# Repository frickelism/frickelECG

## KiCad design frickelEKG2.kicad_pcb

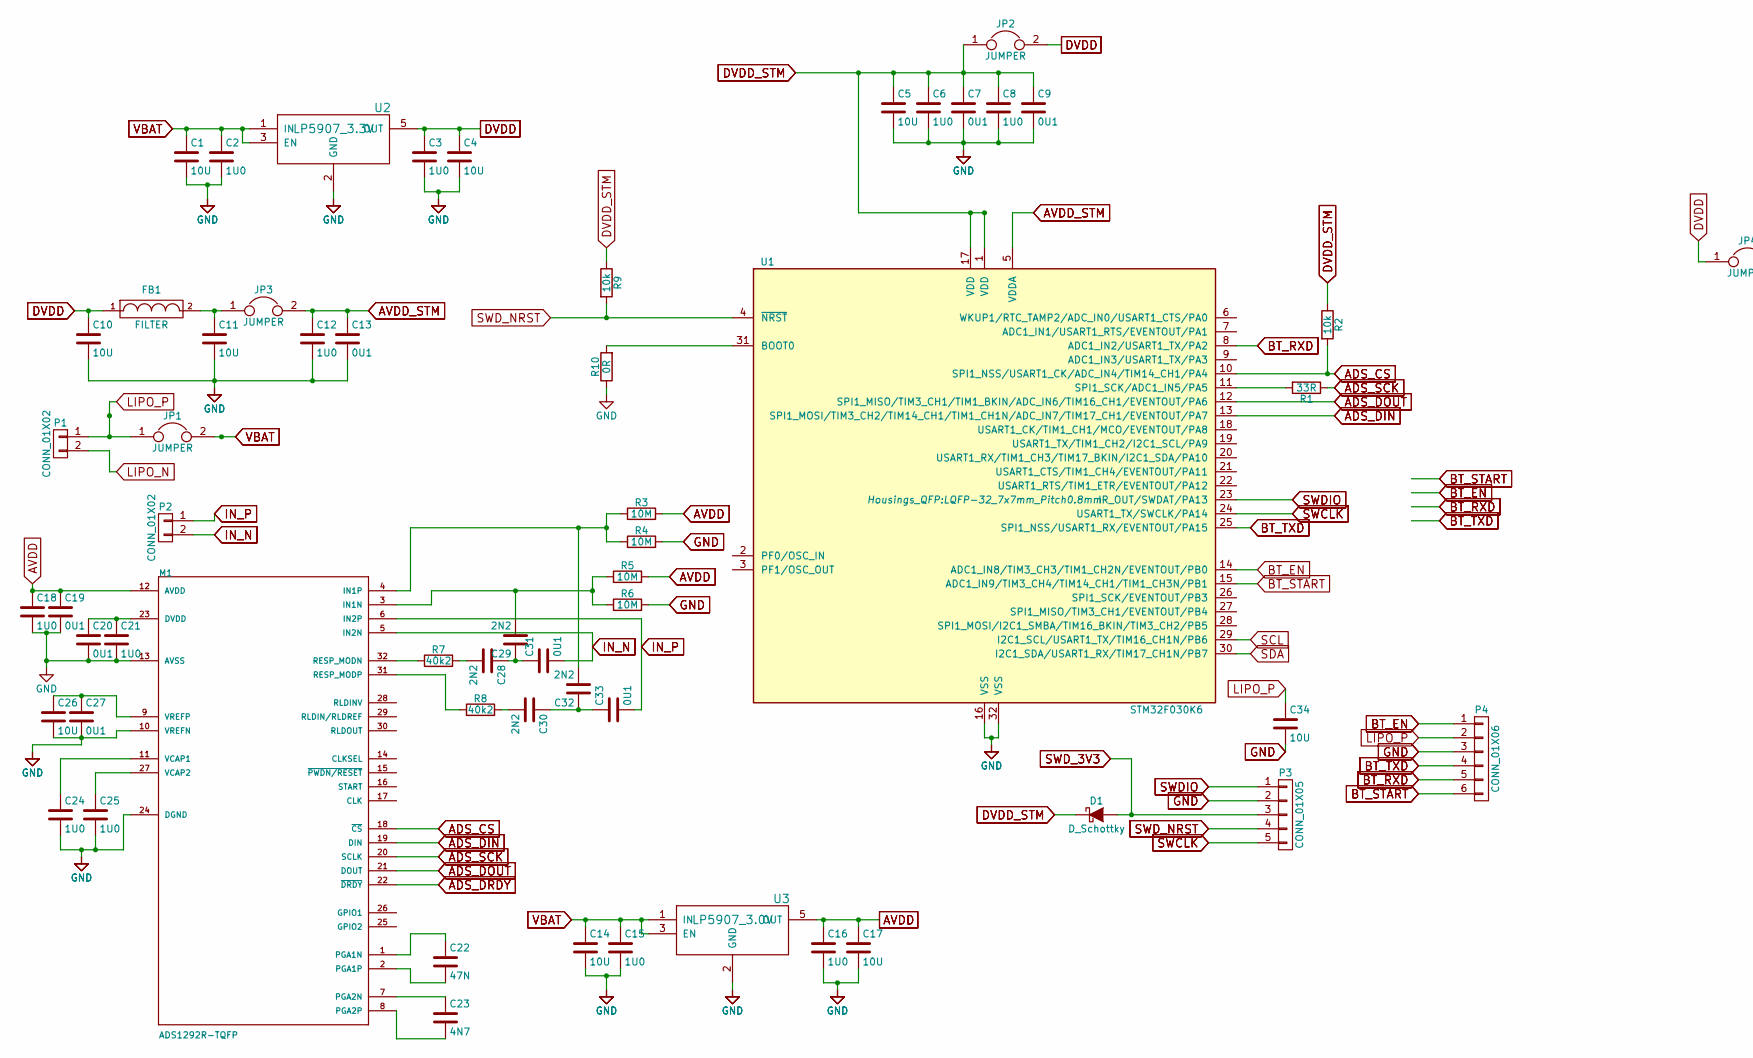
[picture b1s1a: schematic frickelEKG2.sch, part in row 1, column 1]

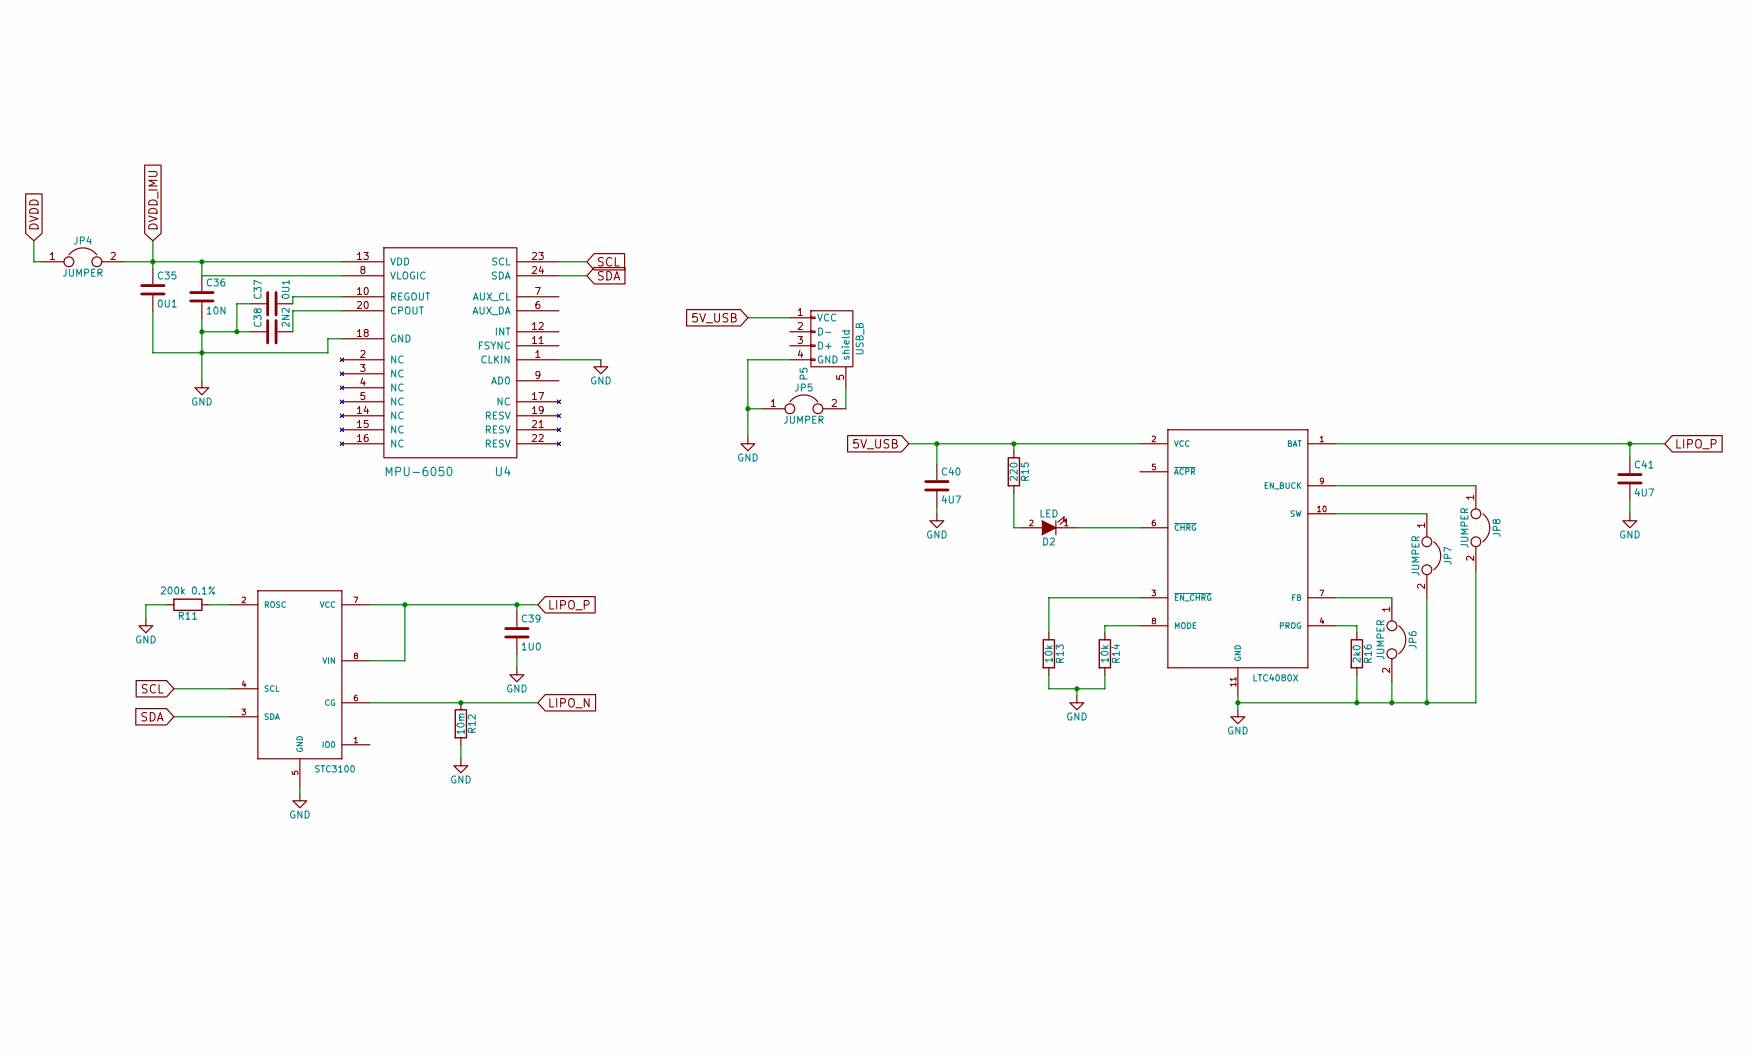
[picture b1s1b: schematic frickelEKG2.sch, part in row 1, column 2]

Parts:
C1, C4, C5, C10, C11, C14, C17, C26, C34: 10U; C_0805
C2, C3, C6, C8, C12, C15, C16, C18, C21, C24, C25, C39: 1U0; C_0603
C7, C9, C13, C19, C20, C27, C35, C37: 0U1; C_0603
C22: 47N; C_1206
C23: 4N7; C_0603
C28, C29, C30, C32, C38: 2N2; C_0603
C31, C33: 0U1; C_1206
C36: 10N; C_0603
C40, C41: 4U7; C_0805
D1: D_Schottky; D_SOD-323
D2: LED; LED_0805
FB1: FILTER; L_0603
JP1, JP2, JP3, JP4, JP5, JP6, JP7, JP8: JUMPER; R_0402
M1: ADS1292R-TQFP; SQFP-S-5X5-32
M2: STC3100; stm_battery-MINISO-8
M3: LTC4080X; ltc_power-LTC4080
P1, P2: CONN_01X02; PINHEAD1-2
P3: CONN_01X05; JST_SH_BM05B-SRSS-TB_05x1.00mm_Straight
P4: CONN_01X06; PINHEAD1-6
P5: USB_B; MICRO-B_USB
R1: 33R; R_0603
R2, R9, R13, R14: 10k; R_0603
R3, R4, R5, R6: 10M; R_0603
R7, R8: 40k2; R_0603
R10: 0R; R_0603
R11: 200k 0.1%; R_0603
R12: 10m; R_0603
R15: 220; R_0603
R16: 2k0; R_0603
U1: STM32F030K6; LQFP-32_7x7mm_Pitch0.8mm
U2: LP5907_3.3V; SOT-23-5
U3: LP5907_3.0V; SOT-23-5
U4: MPU-6050

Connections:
5V_USB: C40.1, M3.2 (VCC), P5.1 (VCC), R15.1
ADS_CS: M1.18 (~CS), R2.2, U1.10 (SPI1_NSS/USART1_CK/ADC_IN4/TIM14_CH1/PA4)
ADS_DIN: M1.19 (DIN), U1.13 (SPI1_MOSI/TIM3_CH2/TIM14_CH1/TIM1_CH1N/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)
ADS_DOUT: M1.21 (DOUT), U1.12 (SPI1_MISO/TIM3_CH1/TIM1_BKIN/ADC_IN6/TI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)
ADS_SCK: M1.20 (SCLK), R1.1
AVDD: C16.1, C17.1, C18.1, C19.1, M1.12 (AVDD), R3.2, R5.2, U3.5 (OUT)
AVDD_STM: C12.1, C13.1, JP3.2, U1.5 (VDDA)
BT_EN: P4.1, U1.14 (ADC1_IN8/TIM3_CH3/TIM1_CH2N/EVENTOUT/PB0)
BT_RXD: P4.5, U1.8 (ADC1_IN2/USART1_TX/PA2)
BT_START: P4.6, U1.15 (ADC1_IN9/TIM3_CH4/TIM14_CH1/TIM1_CH3N/P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)
BT_TXD: P4.4, U1.25 (SPI1_NSS/USART1_RX/EVENTOUT/PA15)
DVDD: C3.1, C4.1, C10.1, FB1.1, JP2.2, JP4.1, U2.5 (OUT)
DVDD_IMU: C35.1, C36.1, JP4.2, U4.8 (VLOGIC), U4.13 (VDD)
DVDD_STM: C5.1, C6.1, C7.1, C8.1, C9.1, D1.1 (K), JP2.1, R2.1, R9.1, U1.1 (VDD), U1.17 (VDD)
GND: C1.2, C2.2, C3.2, C4.2, C5.2, C6.2, C7.2, C8.2, C9.2, C10.2, C11.2, C12.2, C13.2, C14.2, C15.2, C16.2, C17.2, C18.2, C19.2, C20.2, C21.2, C24.2, C25.2, C26.2, C27.2, C34.2, C35.2, C36.2, C37.1, C38.1, C39.2, C40.2, C41.2, JP5.1, JP6.2, JP7.2, JP8.2, M1.10 (VREFN), M1.13 (AVSS), M1.24 (DGND), M2.5 (GND), M3.11 (GND), P3.2, P4.3, P5.4 (GND), R4.2, R6.2, R10.1, R11.2, R12.2, R13.2, R14.2, R16.2, U1.16 (VSS), U1.32 (VSS), U2.2 (GND), U3.2 (GND), U4.1 (CLKIN), U4.18 (GND)
IN_N: C31.2, M1.5 (IN2N), P2.2
IN_P: C33.2, M1.6 (IN2P), P2.1
LIPO_N: M2.6 (CG), P1.2, R12.1
LIPO_P: C34.1, C39.1, C41.1, JP1.1, M2.7 (VCC), M2.8 (VIN), M3.1 (BAT), P1.1, P4.2
unnamed: C11.1, FB1.2, JP3.1
unnamed: C20.1, C21.1, M1.23 (DVDD)
unnamed: C22.1, M1.1 (PGA1N)
unnamed: C22.2, M1.2 (PGA1P)
unnamed: C23.1, M1.7 (PGA2N)
unnamed: C23.2, M1.8 (PGA2P)
unnamed: C24.1, M1.11 (VCAP1)
unnamed: C25.1, M1.27 (VCAP2)
unnamed: C26.1, C27.1, M1.9 (VREFP)
unnamed: C28.1, C29.1, C31.1
unnamed: C28.2, R7.2
unnamed: C29.2, M1.3 (IN1N), R5.1, R6.1
unnamed: C30.1, C32.1, C33.1
unnamed: C30.2, R8.2
unnamed: C32.2, M1.4 (IN1P), R3.1, R4.1
unnamed: C37.2, U4.10 (REGOUT)
unnamed: C38.2, U4.20 (CPOUT)
unnamed: D2.1 (K), M3.6 (~CHRG)
unnamed: D2.2 (A), R15.2
unnamed: JP5.2, P5.5 (shield)
unnamed: JP6.1, M3.7 (FB)
unnamed: JP7.1, M3.10 (SW)
unnamed: JP8.1, M3.9 (EN_BUCK)
unnamed: M1.31 (RESP_MODP), R8.1
unnamed: M1.32 (RESP_MODN), R7.1
unnamed: M2.2 (ROSC), R11.1
unnamed: M3.3 (~EN_CHRG), R13.1
unnamed: M3.4 (PROG), R16.1
unnamed: M3.8 (MODE), R14.1
unnamed: R1.2, U1.11 (SPI1_SCK/ADC1_IN5/PA5)
unnamed: R10.2, U1.31 (BOOT0)
SCL: M2.4 (SCL), U1.29 (I2C1_SCL/USART1_TX/TIM16_CH1N/PB6), U4.23 (SCL)
SDA: M2.3 (SDA), U1.30 (I2C1_SDA/USART1_RX/TIM17_CH1N/PB7), U4.24 (SDA)
SWCLK: P3.5, U1.24 (USART1_TX/SWCLK/PA14)
SWDIO: P3.1, U1.23 (IR_OUT/SWDAT/PA13)
SWD_3V3: D1.2 (A), P3.3
SWD_NRST: P3.4, R9.2, U1.4 (~NRST)
VBAT: C1.1, C2.1, C14.1, C15.1, JP1.2, U2.1 (IN), U2.3 (EN), U3.1 (IN), U3.3 (EN)

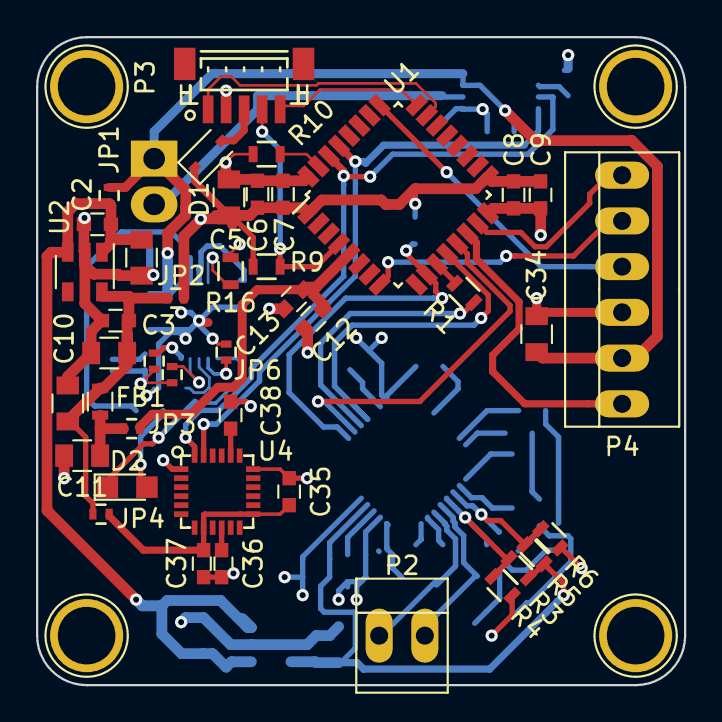
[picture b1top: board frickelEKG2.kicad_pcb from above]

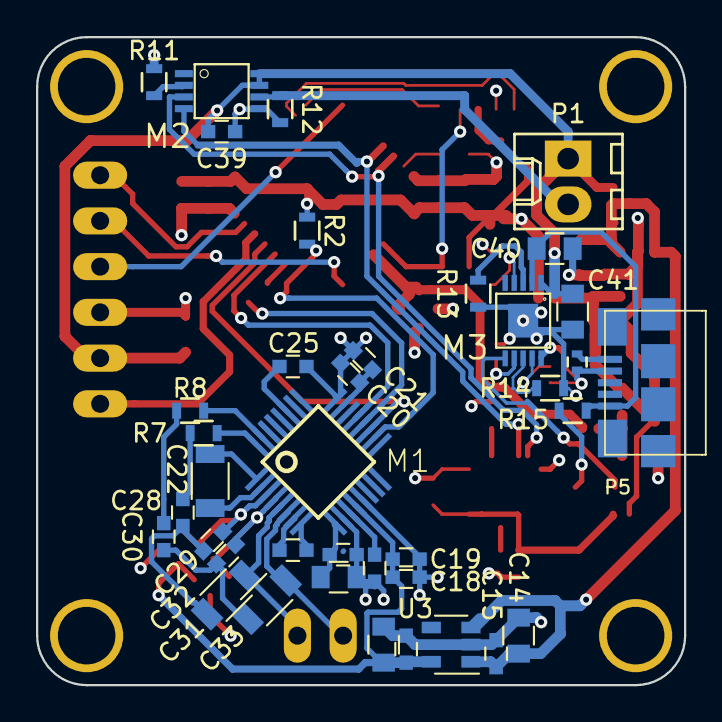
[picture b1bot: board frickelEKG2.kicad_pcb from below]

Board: 4 copper layers, 36.0 x 36.0 mm, 80 parts (38 on the bottom side), 57 nets.

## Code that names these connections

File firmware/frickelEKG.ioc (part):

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Mcu.Name=STM32F030K6Tx
Mcu.Package=LQFP32
Mcu.UserName=STM32F030K6Tx
PA13.Mode=Serial_Wire
PA13.Signal=SYS_SWDIO
PA14.Mode=Serial_Wire
PA14.Signal=SYS_SWCLK
PA15.GPIOParameters=GPIO_Label
PA15.GPIO_Label=BT_RX
PA15.Mode=Asynchronous
PA15.Signal=USART1_RX
PA2.GPIOParameters=GPIO_Label
PA2.GPIO_Label=BT_TX
PA2.Mode=Asynchronous
PA2.Signal=USART1_TX
PA3.GPIOParameters=GPIO_Label
PA3.GPIO_Label=ADS_DRDY
PA3.Signal=GPXTI3
PA4.GPIOParameters=GPIO_Label
PA4.GPIO_Label=ADS_CS
PA4.Mode=NSS_Signal_Hard_Output
PA4.Signal=SPI1_NSS
PA5.GPIOParameters=GPIO_Label
PA5.GPIO_Label=ADS_SCK
PA5.Mode=Full_Duplex_Master
PA5.Signal=SPI1_SCK
PA6.GPIOParameters=GPIO_Label
PA6.GPIO_Label=ADS_MISO
PA6.Mode=Full_Duplex_Master
PA6.Signal=SPI1_MISO
PA7.GPIOParameters=GPIO_Label
PA7.GPIO_Label=ADS_MOSI
PA7.Mode=Full_Duplex_Master
PA7.Signal=SPI1_MOSI
PB0.GPIOParameters=GPIO_Label
PB0.GPIO_Label=BT_EN
PB0.Signal=GPIO_Output
PB1.GPIOParameters=GPIO_Label
PB1.GPIO_Label=BT_START
PB1.Signal=GPIO_Output
PB5.GPIOParameters=GPIO_Label
PB5.GPIO_Label=MPU_INT
PB5.Signal=GPXTI5
PB6.GPIOParameters=GPIO_Label
PB6.GPIO_Label=MPU_SCL
PB6.Mode=I2C
PB6.Signal=I2C1_SCL
PB7.GPIOParameters=GPIO_Label
PB7.GPIO_Label=MPU_SDA
PB7.Mode=I2C
PB7.Signal=I2C1_SDA
RCC.SYSCLKFreq_VALUE=48000000
RCC.SYSCLKSource=RCC_SYSCLKSOURCE_PLLCLK

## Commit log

2017-02-14 init
2017-02-14 added README
2017-02-14 fixed EXTI
